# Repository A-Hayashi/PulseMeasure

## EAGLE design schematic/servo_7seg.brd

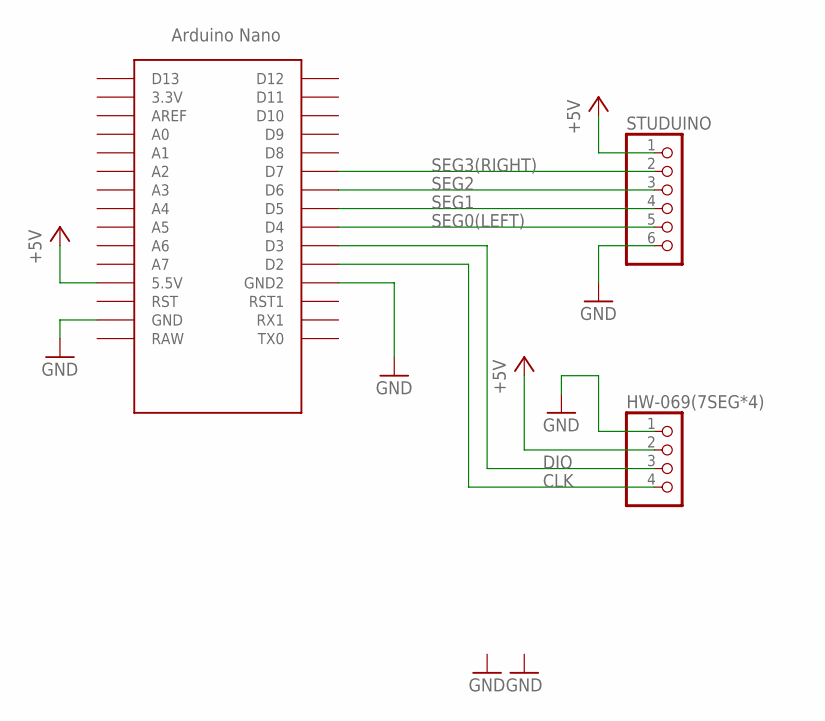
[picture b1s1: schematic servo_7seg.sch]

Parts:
HW-069(7SEG*4): PINHD-1X4; 1X04
STUDUINO: PINHD-1X6; 1X06
U$1: NANO

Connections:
+5V: HW-069(7SEG*4).2, STUDUINO.1, U$1.5V (5.5V)
CLK: HW-069(7SEG*4).4, U$1.D2
DIO: HW-069(7SEG*4).3, U$1.D3
GND: HW-069(7SEG*4).1, STUDUINO.6, U$1.GND, U$1.GND1 (GND2)
SEG0(LEFT): STUDUINO.5, U$1.D4
SEG1: STUDUINO.4, U$1.D5
SEG2: STUDUINO.3, U$1.D6
SEG3(RIGHT): STUDUINO.2, U$1.D7

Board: 2 copper layers, 3 parts (0 on the bottom side), 8 nets, no tracks yet.

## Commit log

2019-01-16 パルス幅計測
2019-01-16 8個分、パルス幅計測できた
2019-01-17 パルス幅計測精度改善
2019-01-19 サーボのパルス幅に応じて7SEGの数字表示
2019-01-19 アーテックのサーボで7SEG表示確認
2019-01-19 回路図追加
